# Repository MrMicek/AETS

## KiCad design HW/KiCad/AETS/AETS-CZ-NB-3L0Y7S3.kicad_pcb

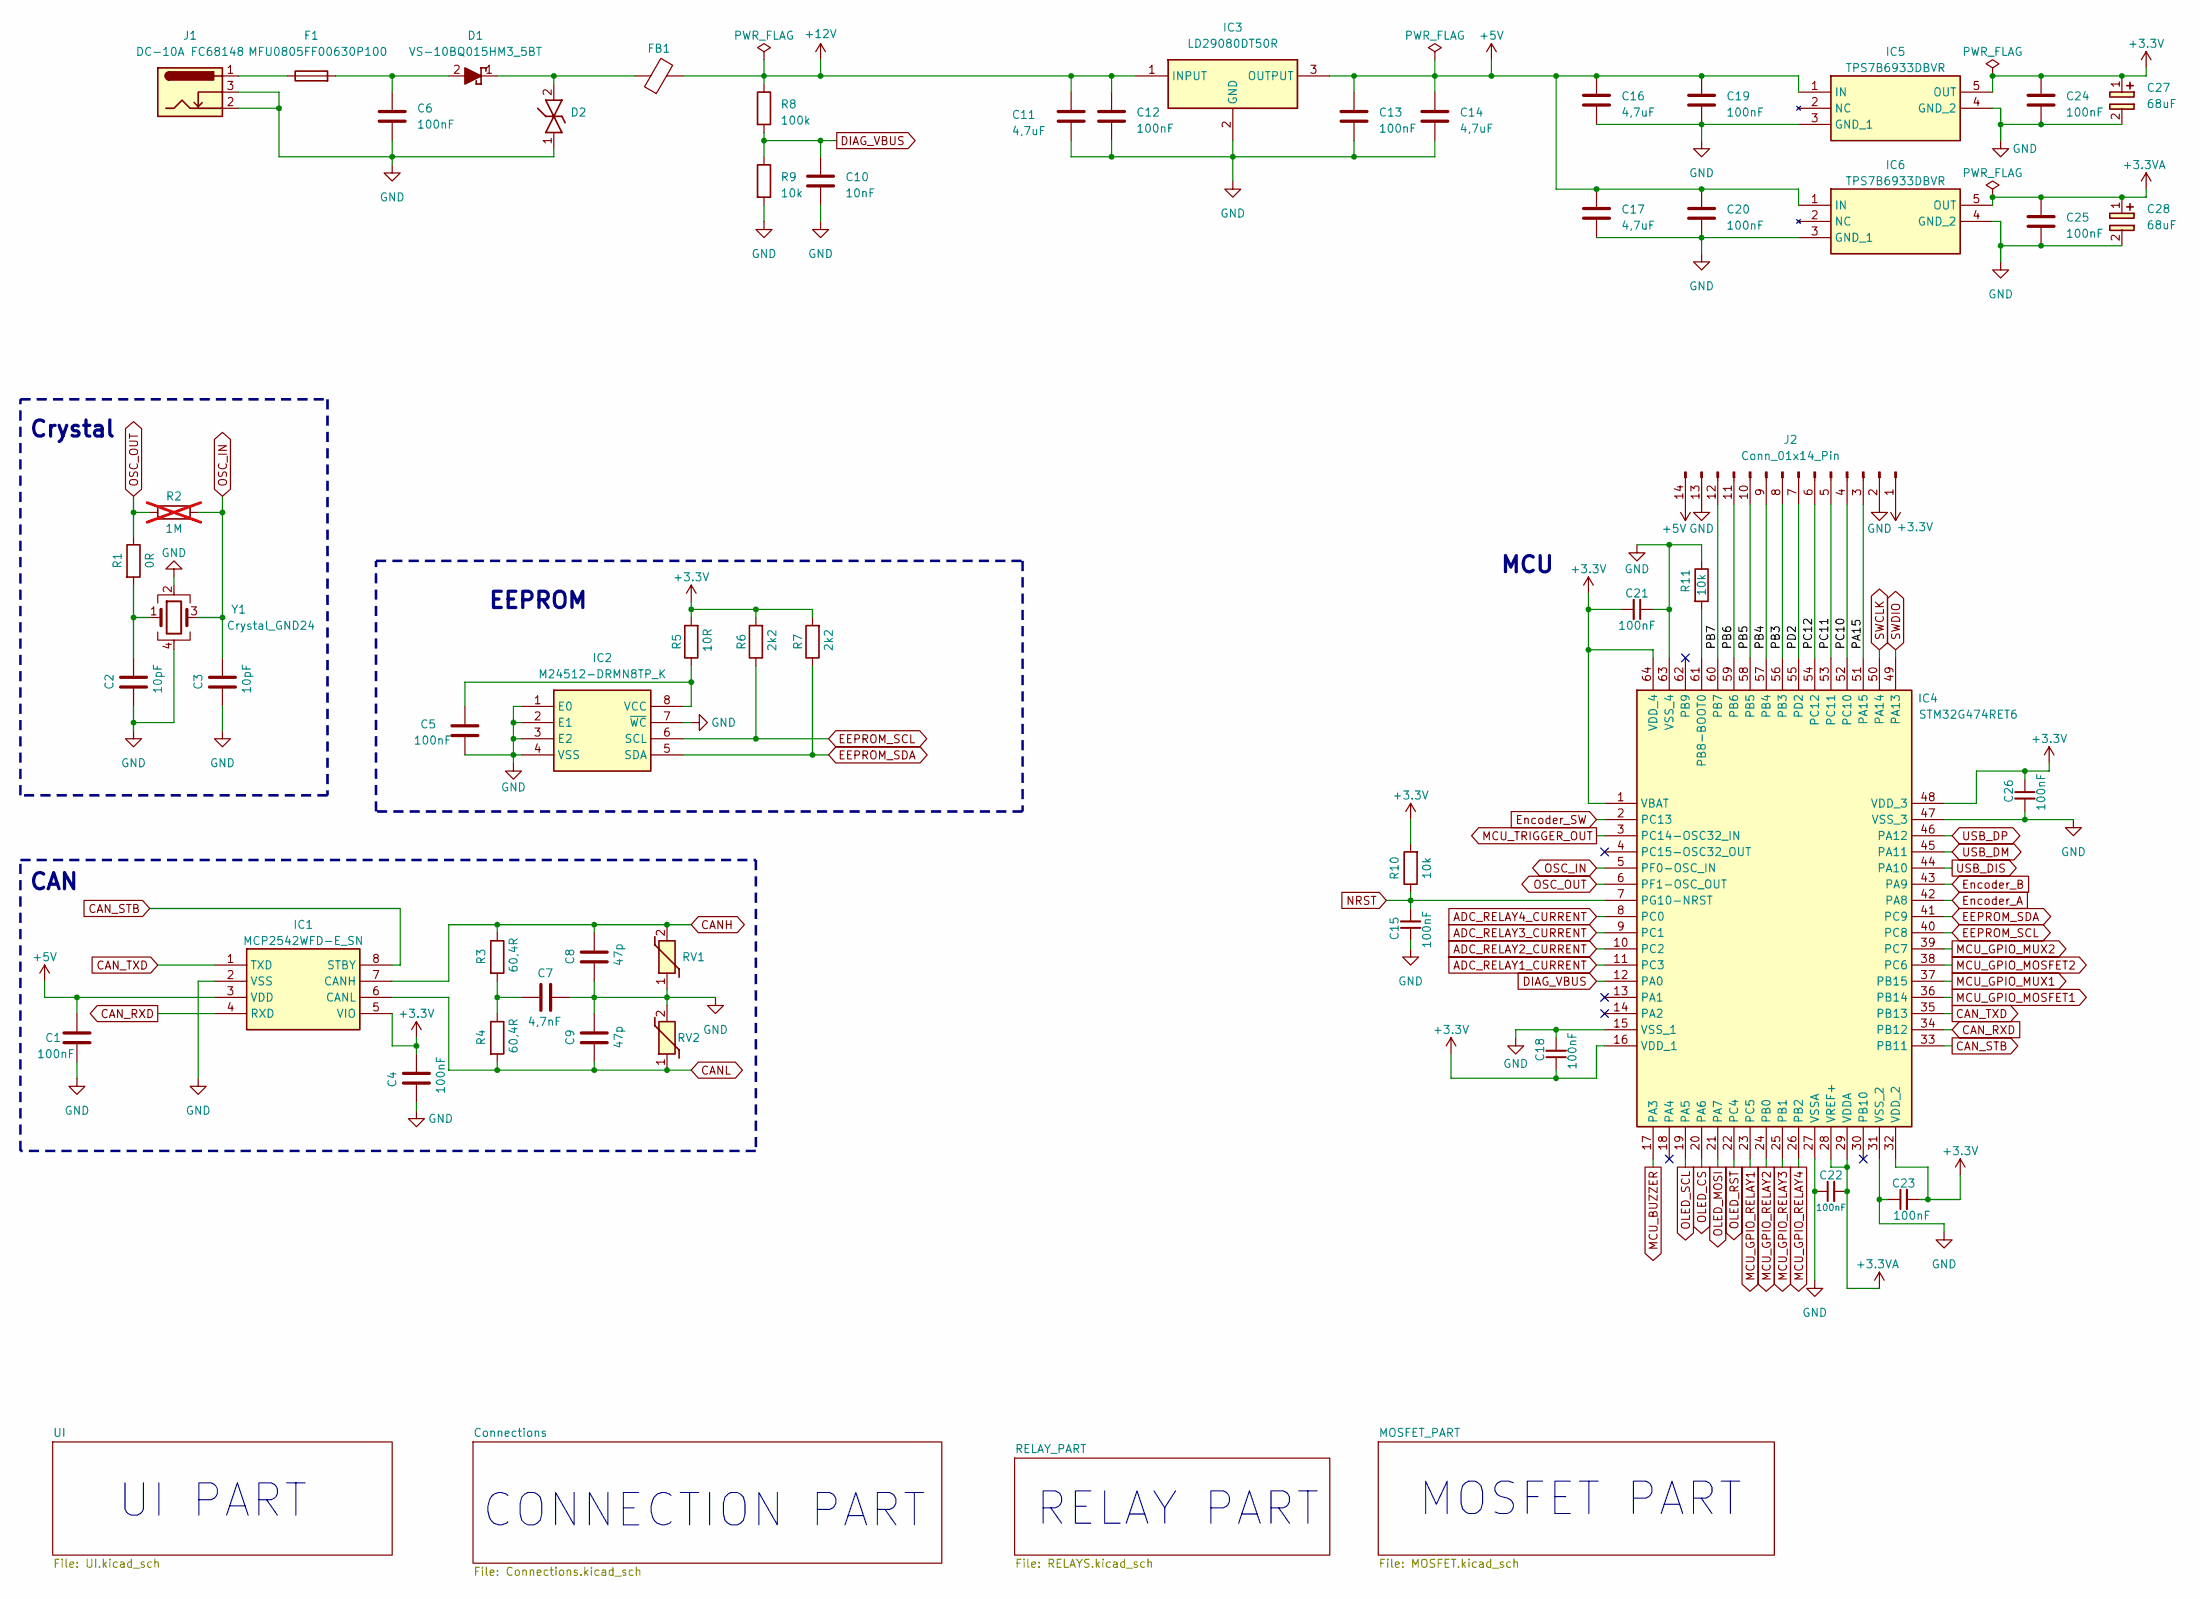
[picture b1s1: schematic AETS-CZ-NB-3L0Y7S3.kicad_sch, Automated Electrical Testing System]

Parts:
C1, C4, C5, C6, C12, C13, C19, C20, C24, C25: 100nF; C_0805_2012Metric
C2, C3: 10pF; C_0603_1608Metric
C7: 4,7nF; C_0805_2012Metric
C8, C9: 47p; C_0805_2012Metric
C10: 10nF; C_0805_2012Metric
C11, C14, C16, C17: 4,7uF; C_1210_3225Metric
C15, C18, C21, C22, C23, C26: 100nF; C_0603_1608Metric
C27, C28: 68uF; EEEHP1H4R7P; Mouser Part Number 667-EEE-FP1C680AL
D1: VS-10BQ015HM3_5BT; DIOM5436X244N; Mouser Part Number 78-VS-10BQ015HM35BT
D2: 1.5B18CA-M3/H; DIOM5436X244N; Manufacturer_Part_Number TESDU5V0 RGG
F1: MFU0805FF00630P100; Fuse_0805_2012Metric
FB1: R_0805_2012Metric_Pad1.20x1.40mm_HandSolder
IC1: MCP2542WFD-E_SN; SOIC127P600X175-8N; Manufacturer_Part_Number MCP2542WFD-E/SN; Mouser Part Number 579-MCP2542WFD-E/SN
IC2: M24512-DRMN8TP_K; SOIC127P600X175-8N; Manufacturer_Part_Number M24512-DRMN8TP/K; Mouser Part Number 511-M24512-DRMN8TP/K
IC3: LD29080DT50R; L4931CDT50TR; Manufacturer_Part_Number L4931CDT50-TR; Mouser Part Number 511-L4931CDT50-TR
IC4: STM32G474RET6; QFP50P1200X1200X160-64N; Manufacturer_Part_Number STM32G474RET6; Mouser Part Number 511-STM32G474RET6
IC5, IC6: TPS7B6933DBVR; SOT95P280X145-5N; Manufacturer_Part_Number TPS7B6950QDBVRQ1; Mouser Part Number 595-TPS7B6950QDBVRQ1
J1: DC-10A FC68148; DC10AFC68148
J2: Conn_01x14_Pin; PinHeader_1x14_P2.54mm_Vertical
R1: 0R; R_0603_1608Metric
R2: 1M; R_0603_1608Metric; not fitted
R3, R4: 60,4R; R_0805_2012Metric
R5: 10R; R_0805_2012Metric
R6, R7: 2k2; R_0805_2012Metric
R8: 100k; R_0805_2012Metric
R9: 10k; R_0805_2012Metric
R10, R11: 10k; R_0603_1608Metric
RV1, RV2: AVR-M1608C270KTACB; VARC1608X90N; Mouser Part Number 810-AVRM1608C270KACB
Y1: Crystal_GND24; ECS4001833JGNTR3

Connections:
+3.3V: C4.1, C18.1, C21.2, C23.2, C24.1, C26.1, C27.1 (+), IC1.5 (VIO), IC4.1 (VBAT), IC4.16 (VDD_1), IC4.32 (VDD_2), IC4.48 (VDD_3), IC4.64 (VDD_4), IC5.5 (OUT), J2.1, R5.2, R6.2, R7.2, R10.2; also elsewhere on the board
+3.3VA: C22.2, C25.1, C28.1 (+), IC4.28 (VREF+), IC4.29 (VDDA), IC6.5 (OUT)
+5V: C1.1, C13.1, C14.1, C16.1, C17.1, C19.1, C20.1, IC1.3 (VDD), IC3.3 (OUTPUT), IC5.1 (IN), IC6.1 (IN), J2.14; also elsewhere on the board
+12V: C11.1, C12.1, FB1.2, IC3.1 (INPUT), R8.1; also elsewhere on the board
/PA15: IC4.51 (PA15), J2.3
/PB3: IC4.56 (PB3), J2.8
/PB4: IC4.57 (PB4), J2.9
/PB5: IC4.58 (PB5), J2.10
/PB6: IC4.59 (PB6), J2.11
/PB7: IC4.60 (PB7), J2.12
/PC10: IC4.52 (PC10), J2.4
/PC11: IC4.53 (PC11), J2.5
/PC12: IC4.54 (PC12), J2.6
/PD2: IC4.55 (PD2), J2.7
ADC_RELAY1_CURRENT: IC4.11 (PC3); also elsewhere on the board
ADC_RELAY2_CURRENT: IC4.10 (PC2); also elsewhere on the board
ADC_RELAY3_CURRENT: IC4.9 (PC1); also elsewhere on the board
ADC_RELAY4_CURRENT: IC4.8 (PC0); also elsewhere on the board
CANH: C8.1, IC1.7 (CANH), R3.1, RV1.2; also elsewhere on the board
CANL: C9.2, IC1.6 (CANL), R4.2, RV2.1; also elsewhere on the board
CAN_RXD: IC1.4 (RXD), IC4.34 (PB12)
CAN_STB: IC1.8 (STBY), IC4.33 (PB11)
CAN_TXD: IC1.1 (TXD), IC4.35 (PB13)
DIAG_VBUS: C10.1, IC4.12 (PA0), R8.2, R9.1
EEPROM_SCL: IC2.6 (SCL), IC4.40 (PC8), R6.1
EEPROM_SDA: IC2.5 (SDA), IC4.41 (PC9), R7.1
Encoder_A: IC4.42 (PA8); also elsewhere on the board
Encoder_B: IC4.43 (PA9); also elsewhere on the board
Encoder_SW: IC4.2 (PC13); also elsewhere on the board
GND: C1.2, C2.2, C3.2, C4.2, C5.2, C6.2, C7.2, C8.2, C9.1, C10.2, C11.2, C12.2, C13.2, C14.2, C15.1, C16.2, C17.2, C18.2, C19.2, C20.2, C21.1, C22.1, C23.1, C24.2, C25.2, C26.2, C27.2 (-), C28.2 (-), D2.1 (K1), IC1.2 (VSS), IC2.1 (E0), IC2.2 (E1), IC2.3 (E2), IC2.4 (VSS), IC2.7 (~WC), IC3.2 (GND), IC4.15 (VSS_1), IC4.27 (VSSA), IC4.31 (VSS_2), IC4.47 (VSS_3), IC4.63 (VSS_4), IC5.3 (GND_1), IC5.4 (GND_2), IC6.3 (GND_1), IC6.4 (GND_2), J1.2, J1.3, J2.2, J2.13, R9.2, R11.1, RV1.1, RV2.2, Y1.2, Y1.4; also elsewhere on the board
MCU_BUZZER: IC4.17 (PA3); also elsewhere on the board
MCU_GPIO_MOSFET1: IC4.36 (PB14); also elsewhere on the board
MCU_GPIO_MOSFET2: IC4.38 (PC6); also elsewhere on the board
MCU_GPIO_MUX1: IC4.37 (PB15); also elsewhere on the board
MCU_GPIO_MUX2: IC4.39 (PC7); also elsewhere on the board
MCU_GPIO_RELAY1: IC4.23 (PC5); also elsewhere on the board
MCU_GPIO_RELAY2: IC4.24 (PB0); also elsewhere on the board
MCU_GPIO_RELAY3: IC4.25 (PB1); also elsewhere on the board
MCU_GPIO_RELAY4: IC4.26 (PB2); also elsewhere on the board
MCU_TRIGGER_OUT: IC4.3 (PC14-OSC32_IN); also elsewhere on the board
NRST: C15.2, IC4.7 (PG10-NRST), R10.1; also elsewhere on the board
unnamed: C2.1, R1.2, Y1.1
unnamed: C7.1, R3.2, R4.1
unnamed: C6.1, D1.2 (A), F1.2
unnamed: D1.1 (K), D2.2 (K2), FB1.1
unnamed: F1.1, J1.1
unnamed: C5.1, IC2.8 (VCC), R5.1
unnamed: IC4.61 (PB8-BOOT0), R11.2
OLED_CS: IC4.20 (PA6); also elsewhere on the board
OLED_MOSI: IC4.21 (PA7); also elsewhere on the board
OLED_RST: IC4.22 (PC4); also elsewhere on the board
OLED_SCL: IC4.19 (PA5); also elsewhere on the board
OSC_IN: C3.1, IC4.5 (PF0-OSC_IN), R2.2, Y1.3
OSC_OUT: IC4.6 (PF1-OSC_OUT), R1.1, R2.1
SWCLK: IC4.50 (PA14); also elsewhere on the board
SWDIO: IC4.49 (PA13); also elsewhere on the board
USB_DIS: IC4.44 (PA10); also elsewhere on the board
USB_DM: IC4.45 (PA11); also elsewhere on the board
USB_DP: IC4.46 (PA12); also elsewhere on the board

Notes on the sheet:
MOSFET PART
RELAY PART
MCU
Crystal
UI PART
CAN
EEPROM
CONNECTION PART

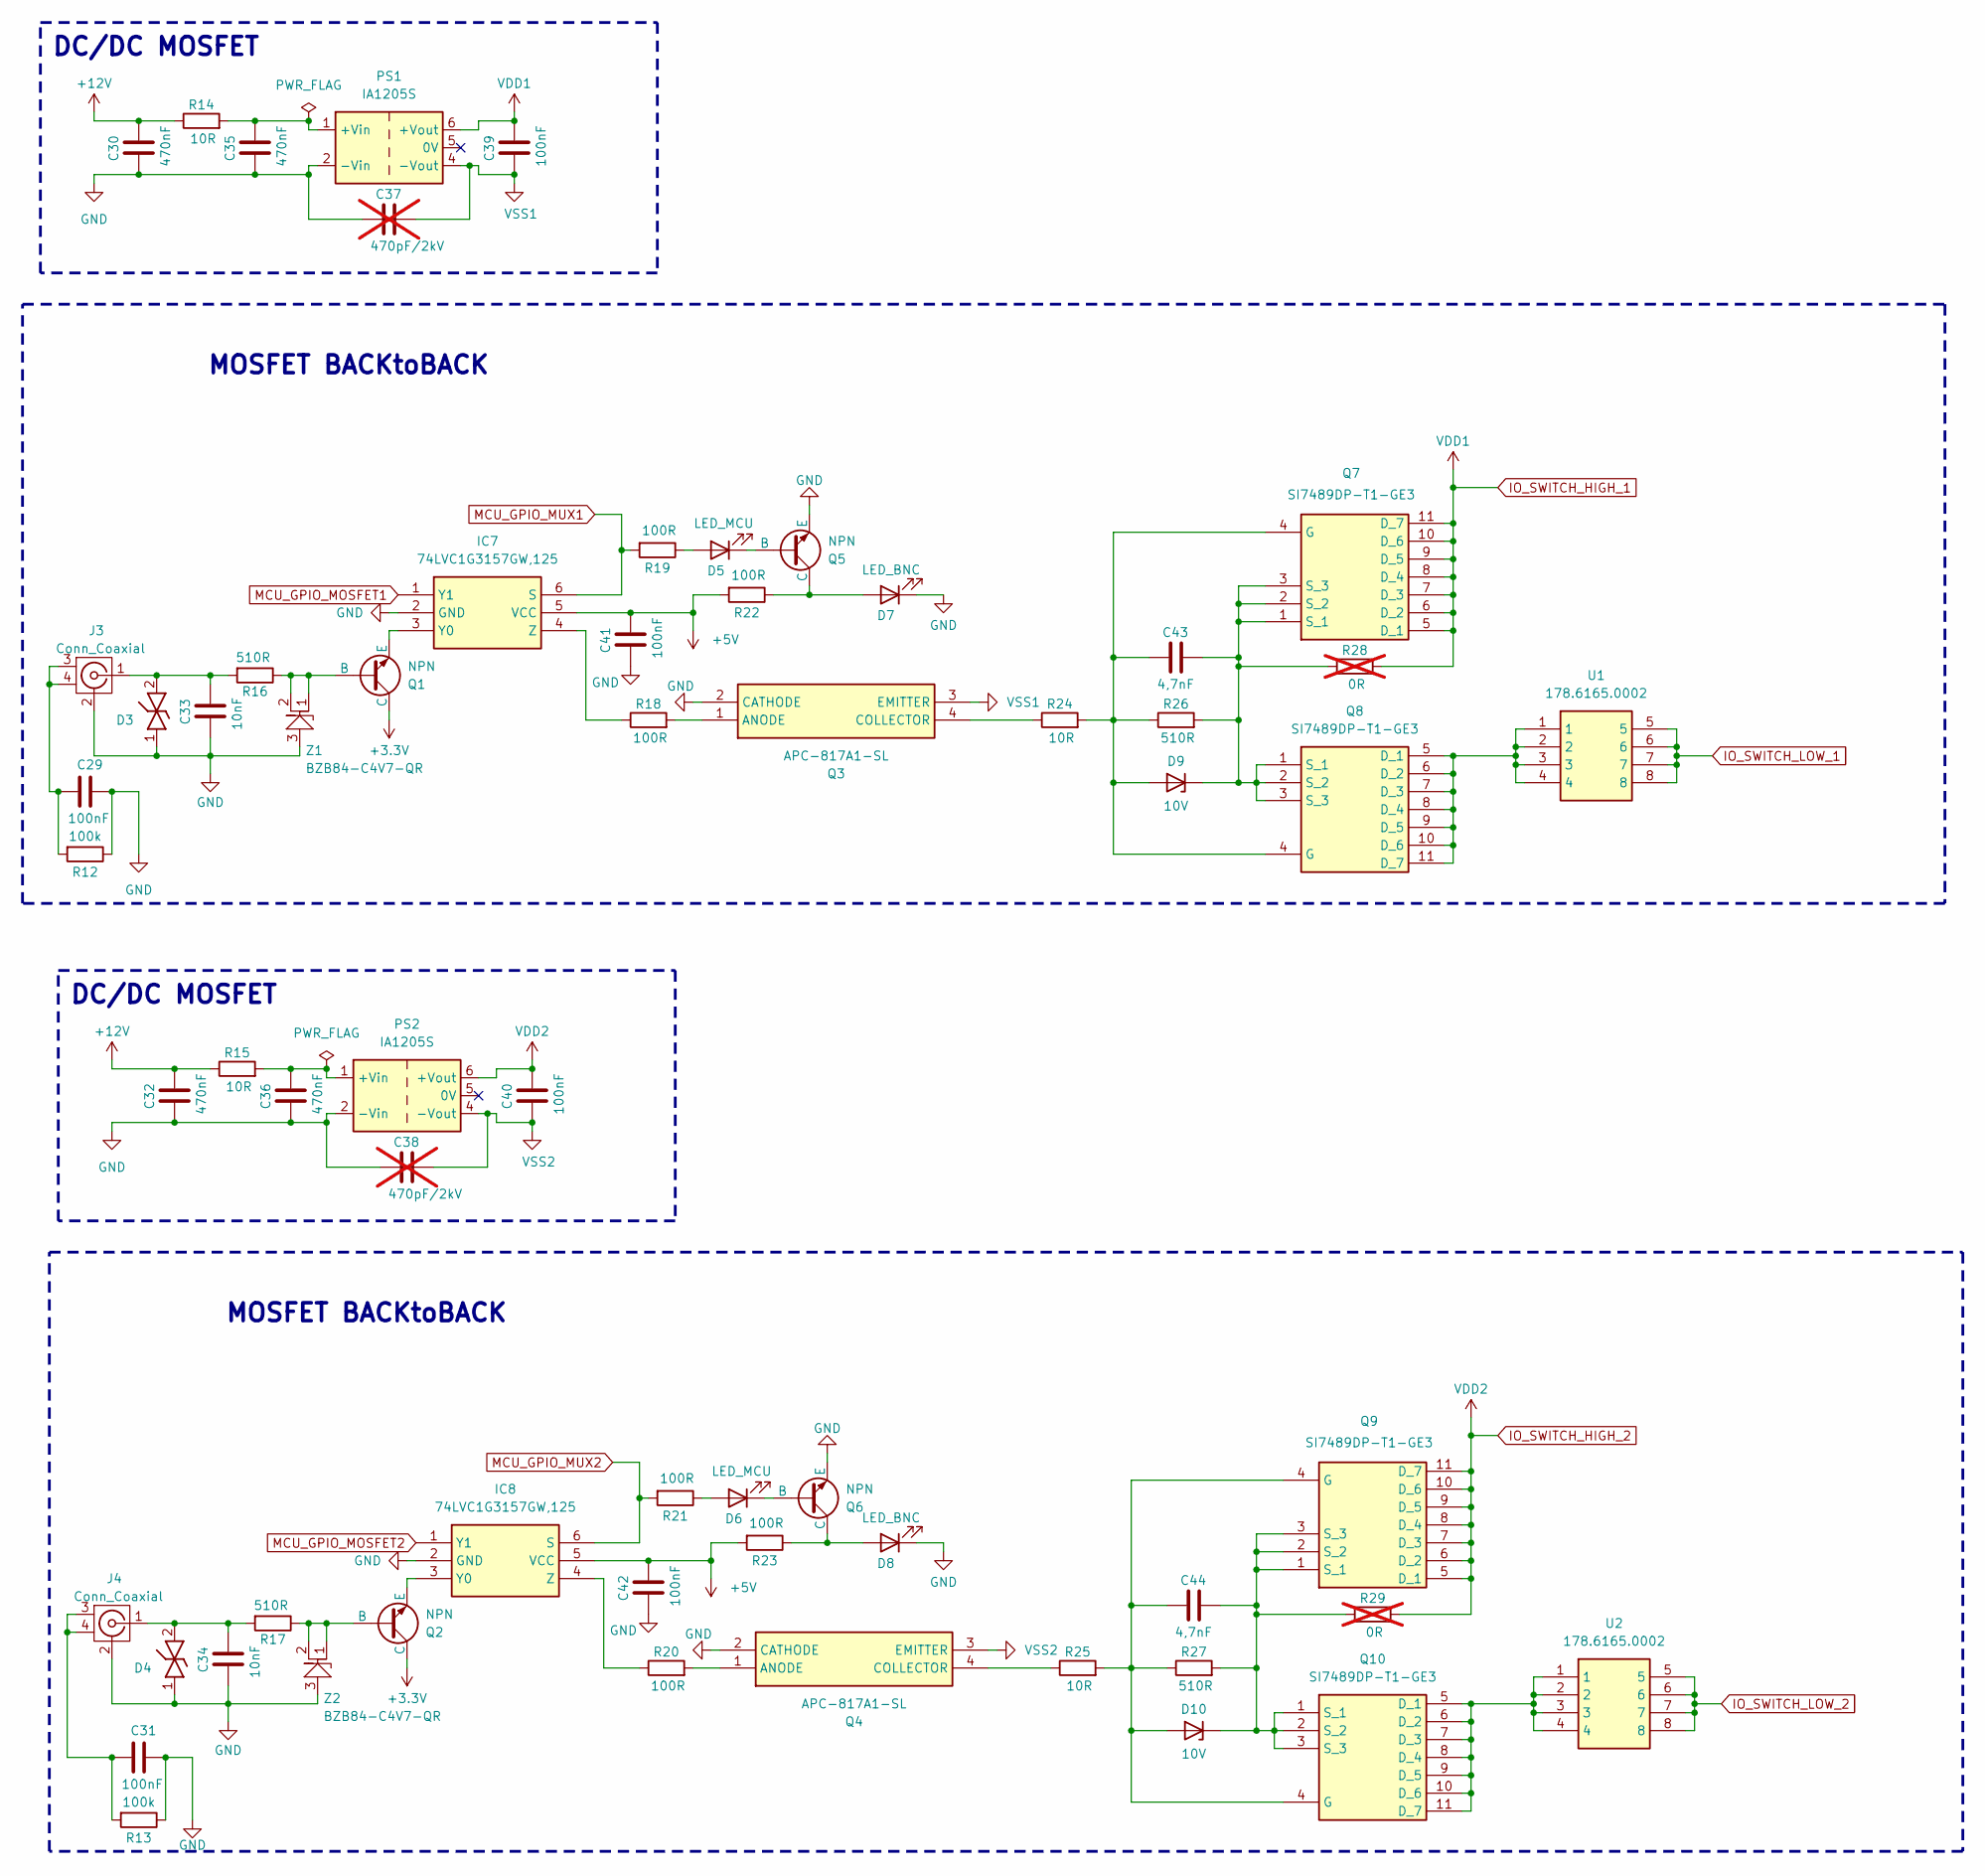
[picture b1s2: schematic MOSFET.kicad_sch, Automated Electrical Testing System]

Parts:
C29, C31, C39, C40, C41, C42: 100nF; C_0805_2012Metric
C30, C32, C35, C36: 470nF; C_0805_2012Metric
C33, C34: 10nF; C_0805_2012Metric
C37, C38: 470pF/2kV; C_1210_3225Metric; not fitted
C43, C44: 4,7nF; C_0805_2012Metric
D3, D4: TESDU5V0 RGG; DIONC1608X70N; Manufacturer_Part_Number TESDU5V0 RGG
D5, D6: LED_MCU; LED_D3.0mm
D7, D8: LED_BNC; LED_D3.0mm
D9, D10: 10V; SODFL5026X125N
IC7, IC8: 74LVC1G3157GW,125; 74LVC1G3157GW125; Manufacturer_Part_Number 74LVC1G3157GW,125; Mouser Part Number 771-LVC1G3157GW125
J3, J4: Conn_Coaxial; VBI211
PS1, PS2: IA1205S; Converter_DCDC_XP_POWER-IAxxxxS_THT
Q1, Q2, Q5, Q6: NPN; SOT95P240X120-3N
Q3, Q4: APC-817A1-SL; APC817A1SL; Manufacturer_Part_Number APC-817A1-SL
Q7, Q8, Q9, Q10: SI7489DP-T1-GE3; SI7141DPT1GE3; Manufacturer_Part_Number SI7489DP-T1-GE3; Mouser Part Number 781-SI7489DP-T1-GE3
R12, R13: 100k; R_0805_2012Metric
R14, R15, R24, R25: 10R; R_0805_2012Metric
R16, R17, R26, R27: 510R; R_0805_2012Metric
R18, R19, R20, R21, R22, R23: 100R; R_0805_2012Metric
R28, R29: 0R; R_0603_1608Metric; not fitted
U1, U2: 178.6165.0002; 17861650002; Mouser Part Number 576-178.6165.0002
Z1, Z2: BZB84-C4V7-QR; SOT95P230X110-3N; Manufacturer_Part_Number BZB84-C4V7-QR

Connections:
+3.3V: Q1.3 (C), Q2.3 (C); also elsewhere on the board
+5V: C41.1, C42.1, IC7.5 (VCC), IC8.5 (VCC), R22.2, R23.2; also elsewhere on the board
+12V: C30.1, C32.1, R14.1, R15.1; also elsewhere on the board
GND: C29.1, C30.2, C31.1, C32.2, C33.2, C34.2, C35.2, C36.2, C37.2, C38.2, C41.2, C42.2, D3.1 (K1), D4.1 (K1), D7.1 (K), D8.1 (K), IC7.2 (GND), IC8.2 (GND), J3.2 (Ext), J4.2 (Ext), PS1.2 (-Vin), PS2.2 (-Vin), Q3.2 (CATHODE), Q4.2 (CATHODE), Q5.2 (E), Q6.2 (E), R12.1, R13.1, Z1.3, Z2.3; also elsewhere on the board
IO_SWITCH_HIGH_1: C39.1, PS1.6 (+Vout), Q7.5 (D_1), Q7.6 (D_2), Q7.7 (D_3), Q7.8 (D_4), Q7.9 (D_5), Q7.10 (D_6), Q7.11 (D_7), R28.2; also elsewhere on the board
IO_SWITCH_HIGH_2: C40.1, PS2.6 (+Vout), Q9.5 (D_1), Q9.6 (D_2), Q9.7 (D_3), Q9.8 (D_4), Q9.9 (D_5), Q9.10 (D_6), Q9.11 (D_7), R29.2; also elsewhere on the board
IO_SWITCH_LOW_1: U1.5, U1.6, U1.7, U1.8; also elsewhere on the board
IO_SWITCH_LOW_2: U2.5, U2.6, U2.7, U2.8; also elsewhere on the board
MCU_GPIO_MOSFET1: IC7.1 (Y1); also elsewhere on the board
MCU_GPIO_MOSFET2: IC8.1 (Y1); also elsewhere on the board
MCU_GPIO_MUX1: IC7.6 (S), R19.2; also elsewhere on the board
MCU_GPIO_MUX2: IC8.6 (S), R21.2; also elsewhere on the board
unnamed: C29.2, J3.3, J3.4, R12.2
unnamed: C31.2, J4.3, J4.4, R13.2
unnamed: C33.1, D3.2 (K2), J3.1 (In), R16.2
unnamed: C34.1, D4.2 (K2), J4.1 (In), R17.2
unnamed: D5.2 (A), R19.1
unnamed: D5.1 (K), Q5.1 (B)
unnamed: D6.2 (A), R21.1
unnamed: D6.1 (K), Q6.1 (B)
unnamed: D7.2 (A), Q5.3 (C), R22.1
unnamed: D8.2 (A), Q6.3 (C), R23.1
unnamed: C43.2, D9.2 (A), Q7.4 (G), Q8.4 (G), R24.2, R26.1
unnamed: C43.1, D9.1 (K), Q7.1 (S_1), Q7.2 (S_2), Q7.3 (S_3), Q8.1 (S_1), Q8.2 (S_2), Q8.3 (S_3), R26.2, R28.1
unnamed: C44.2, D10.2 (A), Q9.4 (G), Q10.4 (G), R25.2, R27.1
unnamed: C44.1, D10.1 (K), Q9.1 (S_1), Q9.2 (S_2), Q9.3 (S_3), Q10.1 (S_1), Q10.2 (S_2), Q10.3 (S_3), R27.2, R29.1
unnamed: IC7.3 (Y0), Q1.2 (E)
unnamed: IC7.4 (Z), R18.1
unnamed: IC8.3 (Y0), Q2.2 (E)
unnamed: IC8.4 (Z), R20.1
unnamed: C35.1, PS1.1 (+Vin), R14.2
unnamed: C36.1, PS2.1 (+Vin), R15.2
unnamed: Q1.1 (B), R16.1, Z1.1, Z1.2
unnamed: Q2.1 (B), R17.1, Z2.1, Z2.2
unnamed: Q3.1 (ANODE), R18.2
unnamed: Q3.4 (COLLECTOR), R24.1
unnamed: Q4.1 (ANODE), R20.2
unnamed: Q4.4 (COLLECTOR), R25.1
unnamed: Q8.5 (D_1), Q8.6 (D_2), Q8.7 (D_3), Q8.8 (D_4), Q8.9 (D_5), Q8.10 (D_6), Q8.11 (D_7), U1.1, U1.2, U1.3, U1.4
unnamed: Q10.5 (D_1), Q10.6 (D_2), Q10.7 (D_3), Q10.8 (D_4), Q10.9 (D_5), Q10.10 (D_6), Q10.11 (D_7), U2.1, U2.2, U2.3, U2.4
VSS1: C37.1, C39.2, PS1.4 (-Vout), Q3.3 (EMITTER)
VSS2: C38.1, C40.2, PS2.4 (-Vout), Q4.3 (EMITTER)

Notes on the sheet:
MOSFET BACKtoBACK
DC/DC MOSFET

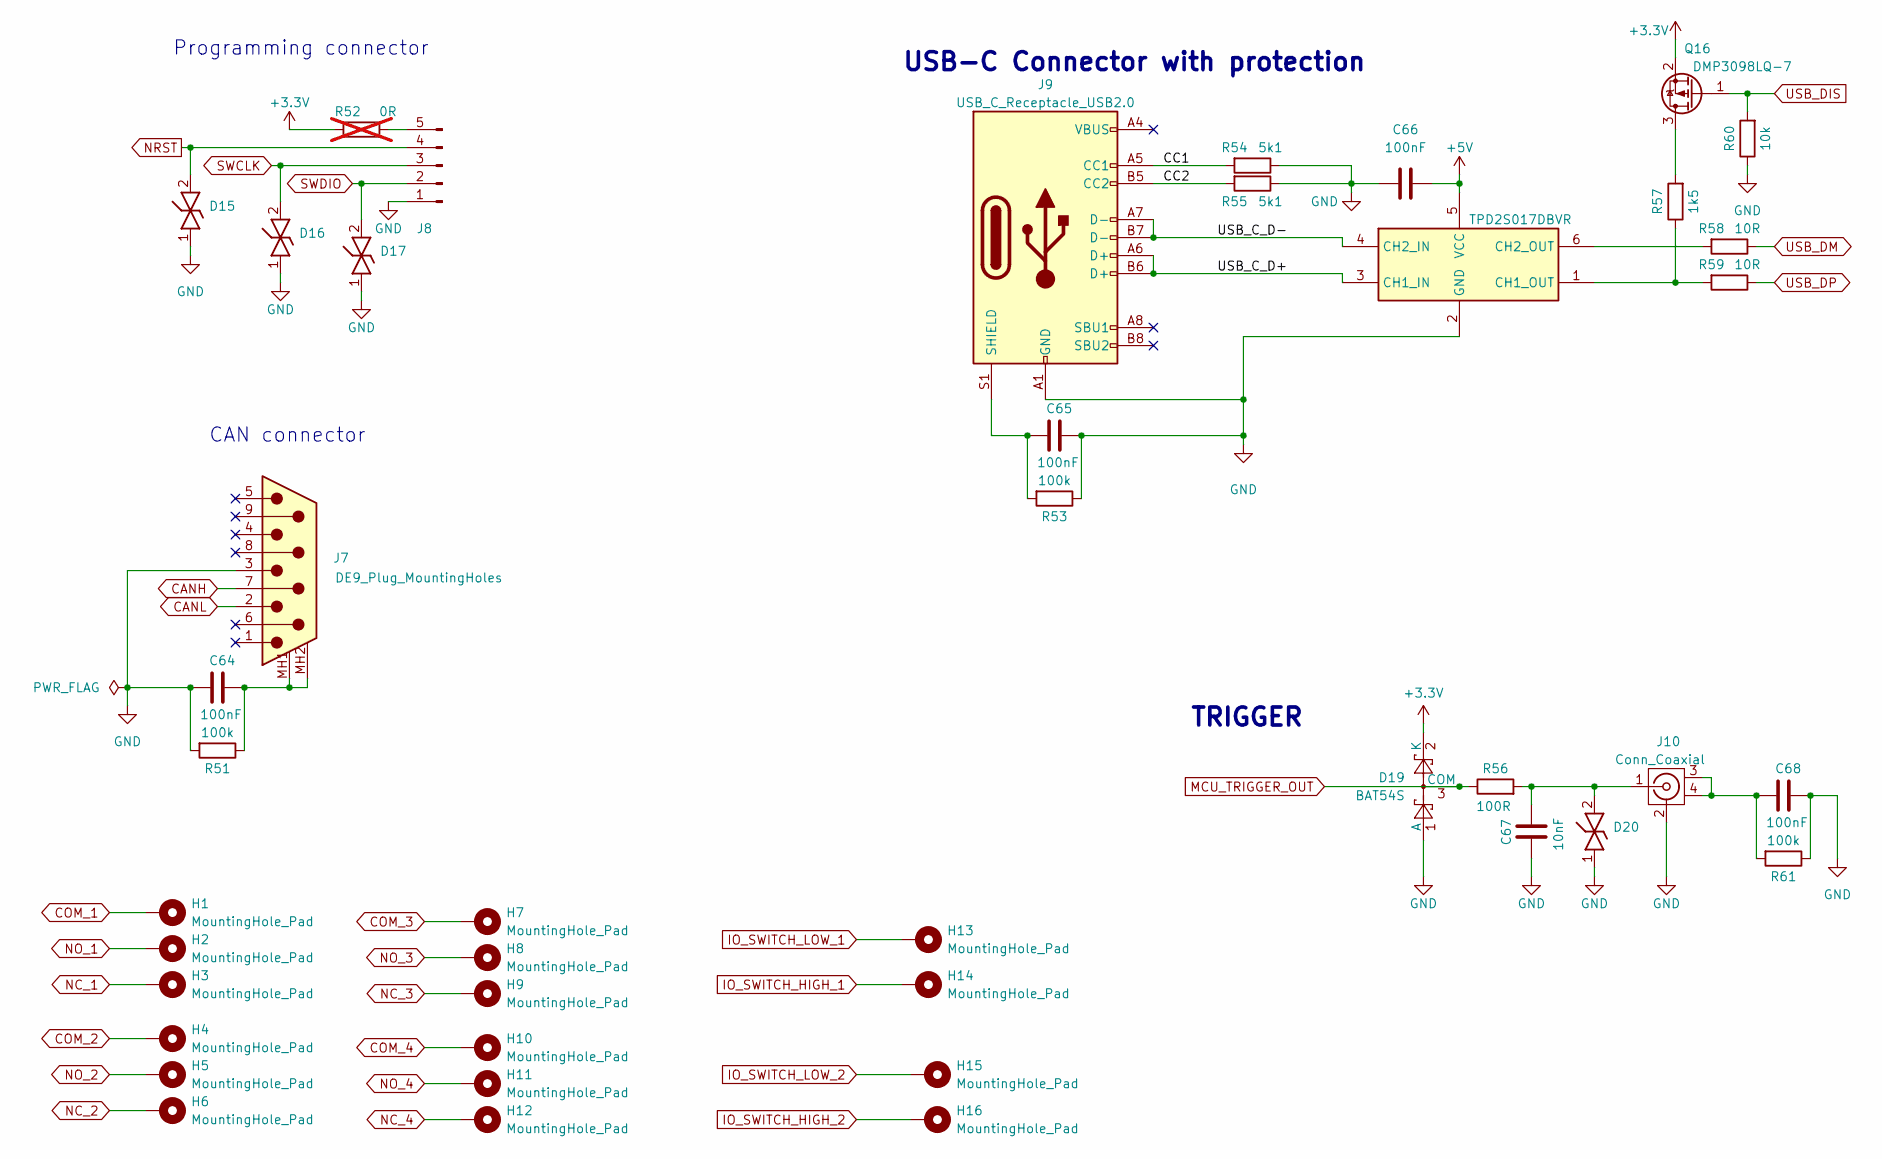
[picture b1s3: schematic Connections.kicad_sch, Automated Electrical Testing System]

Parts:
C64, C65, C66, C68: 100nF; C_0805_2012Metric
C67: 10nF; C_0805_2012Metric
D15, D16, D17, D20: TESDU5V0 RGG; DIONC1608X70N; Manufacturer_Part_Number TESDU5V0 RGG
D18: TPD2S017DBVR; SOT95P280X145-6N; Manufacturer_Part_Number TPD2S017DBVR; Mouser Part Number 595-TPD2S017DBVR
D19: BAT54S; SOT-23
H1, H2, H3, H4, H5, H6, H7, H8, H9, H10, H11, H12, H13, H14, H15, H16: MountingHole_Pad; MountingHole_2.2mm_M2_Pad_Via
J7: DE9_Plug_MountingHoles; G17C0910132EU
J8: Conn_01x05_Pin; PinHeader_1x05_P2.54mm_Vertical
J9: USB_C_Receptacle_USB2.0; USB_C_Receptacle_GCT_USB4105-xx-A_16P_TopMnt_Horizontal
J10: Conn_Coaxial; VBI211
Q16: DMP3098LQ-7; SOT96P240X110-3N
R51, R53, R61: 100k; R_0805_2012Metric
R52: 0R; R_0603_1608Metric; not fitted
R54, R55: 5k1; R_0805_2012Metric
R56: 100R; R_0805_2012Metric
R57: 1k5; R_0603_1608Metric
R58, R59: 10R; R_0805_2012Metric
R60: 10k; R_0805_2012Metric

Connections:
+3.3V: D19.2 (K), Q16.2 (S), R52.1; also elsewhere on the board
+5V: C66.2, D18.5 (VCC); also elsewhere on the board
/Connections/CC1: J9.A5 (CC1), R54.2
/Connections/CC2: J9.B5 (CC2), R55.2
/Connections/USB_C_D+: D18.3 (CH1_IN), J9.A6 (D+), J9.B6 (D+)
/Connections/USB_C_D-: D18.4 (CH2_IN), J9.A7 (D-), J9.B7 (D-)
CANH: J7.7; also elsewhere on the board
CANL: J7.2; also elsewhere on the board
COM_1: H1.1; also elsewhere on the board
COM_2: H4.1; also elsewhere on the board
COM_3: H7.1; also elsewhere on the board
COM_4: H10.1; also elsewhere on the board
GND: C64.2, C65.1, C66.1, C67.2, C68.1, D15.1 (K1), D16.1 (K1), D17.1 (K1), D18.2 (GND), D19.1 (A), D20.1 (K1), J7.3, J8.1, J9.A1 (GND), J9.A12 (GND), J9.B1 (GND), J9.B12 (GND), J10.2 (Ext), R51.2, R53.1, R54.1, R55.1, R60.1, R61.1; also elsewhere on the board
IO_SWITCH_HIGH_1: H14.1; also elsewhere on the board
IO_SWITCH_HIGH_2: H16.1; also elsewhere on the board
IO_SWITCH_LOW_1: H13.1; also elsewhere on the board
IO_SWITCH_LOW_2: H15.1; also elsewhere on the board
MCU_TRIGGER_OUT: D19.3 (COM), R56.1; also elsewhere on the board
NC_1: H3.1; also elsewhere on the board
NC_2: H6.1; also elsewhere on the board
NC_3: H9.1; also elsewhere on the board
NC_4: H12.1; also elsewhere on the board
NO_1: H2.1; also elsewhere on the board
NO_2: H5.1; also elsewhere on the board
NO_3: H8.1; also elsewhere on the board
NO_4: H11.1; also elsewhere on the board
NRST: D15.2 (K2), J8.4; also elsewhere on the board
unnamed: C64.1, J7.MH1 (PAD), J7.MH2 (PAD), R51.1
unnamed: C68.2, J10.3, J10.4, R61.2
unnamed: D18.1 (CH1_OUT), R57.1, R59.2
unnamed: D18.6 (CH2_OUT), R58.2
unnamed: C67.1, D20.2 (K2), J10.1 (In), R56.2
unnamed: J8.5, R52.2
unnamed: C65.2, J9.S1 (SHIELD), R53.2
unnamed: Q16.3 (D), R57.2
SWCLK: D16.2 (K2), J8.3; also elsewhere on the board
SWDIO: D17.2 (K2), J8.2; also elsewhere on the board
USB_DIS: Q16.1 (G), R60.2; also elsewhere on the board
USB_DM: R58.1; also elsewhere on the board
USB_DP: R59.1; also elsewhere on the board

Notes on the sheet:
Programming connector
TRIGGER
USB-C Connector with protection
CAN connector

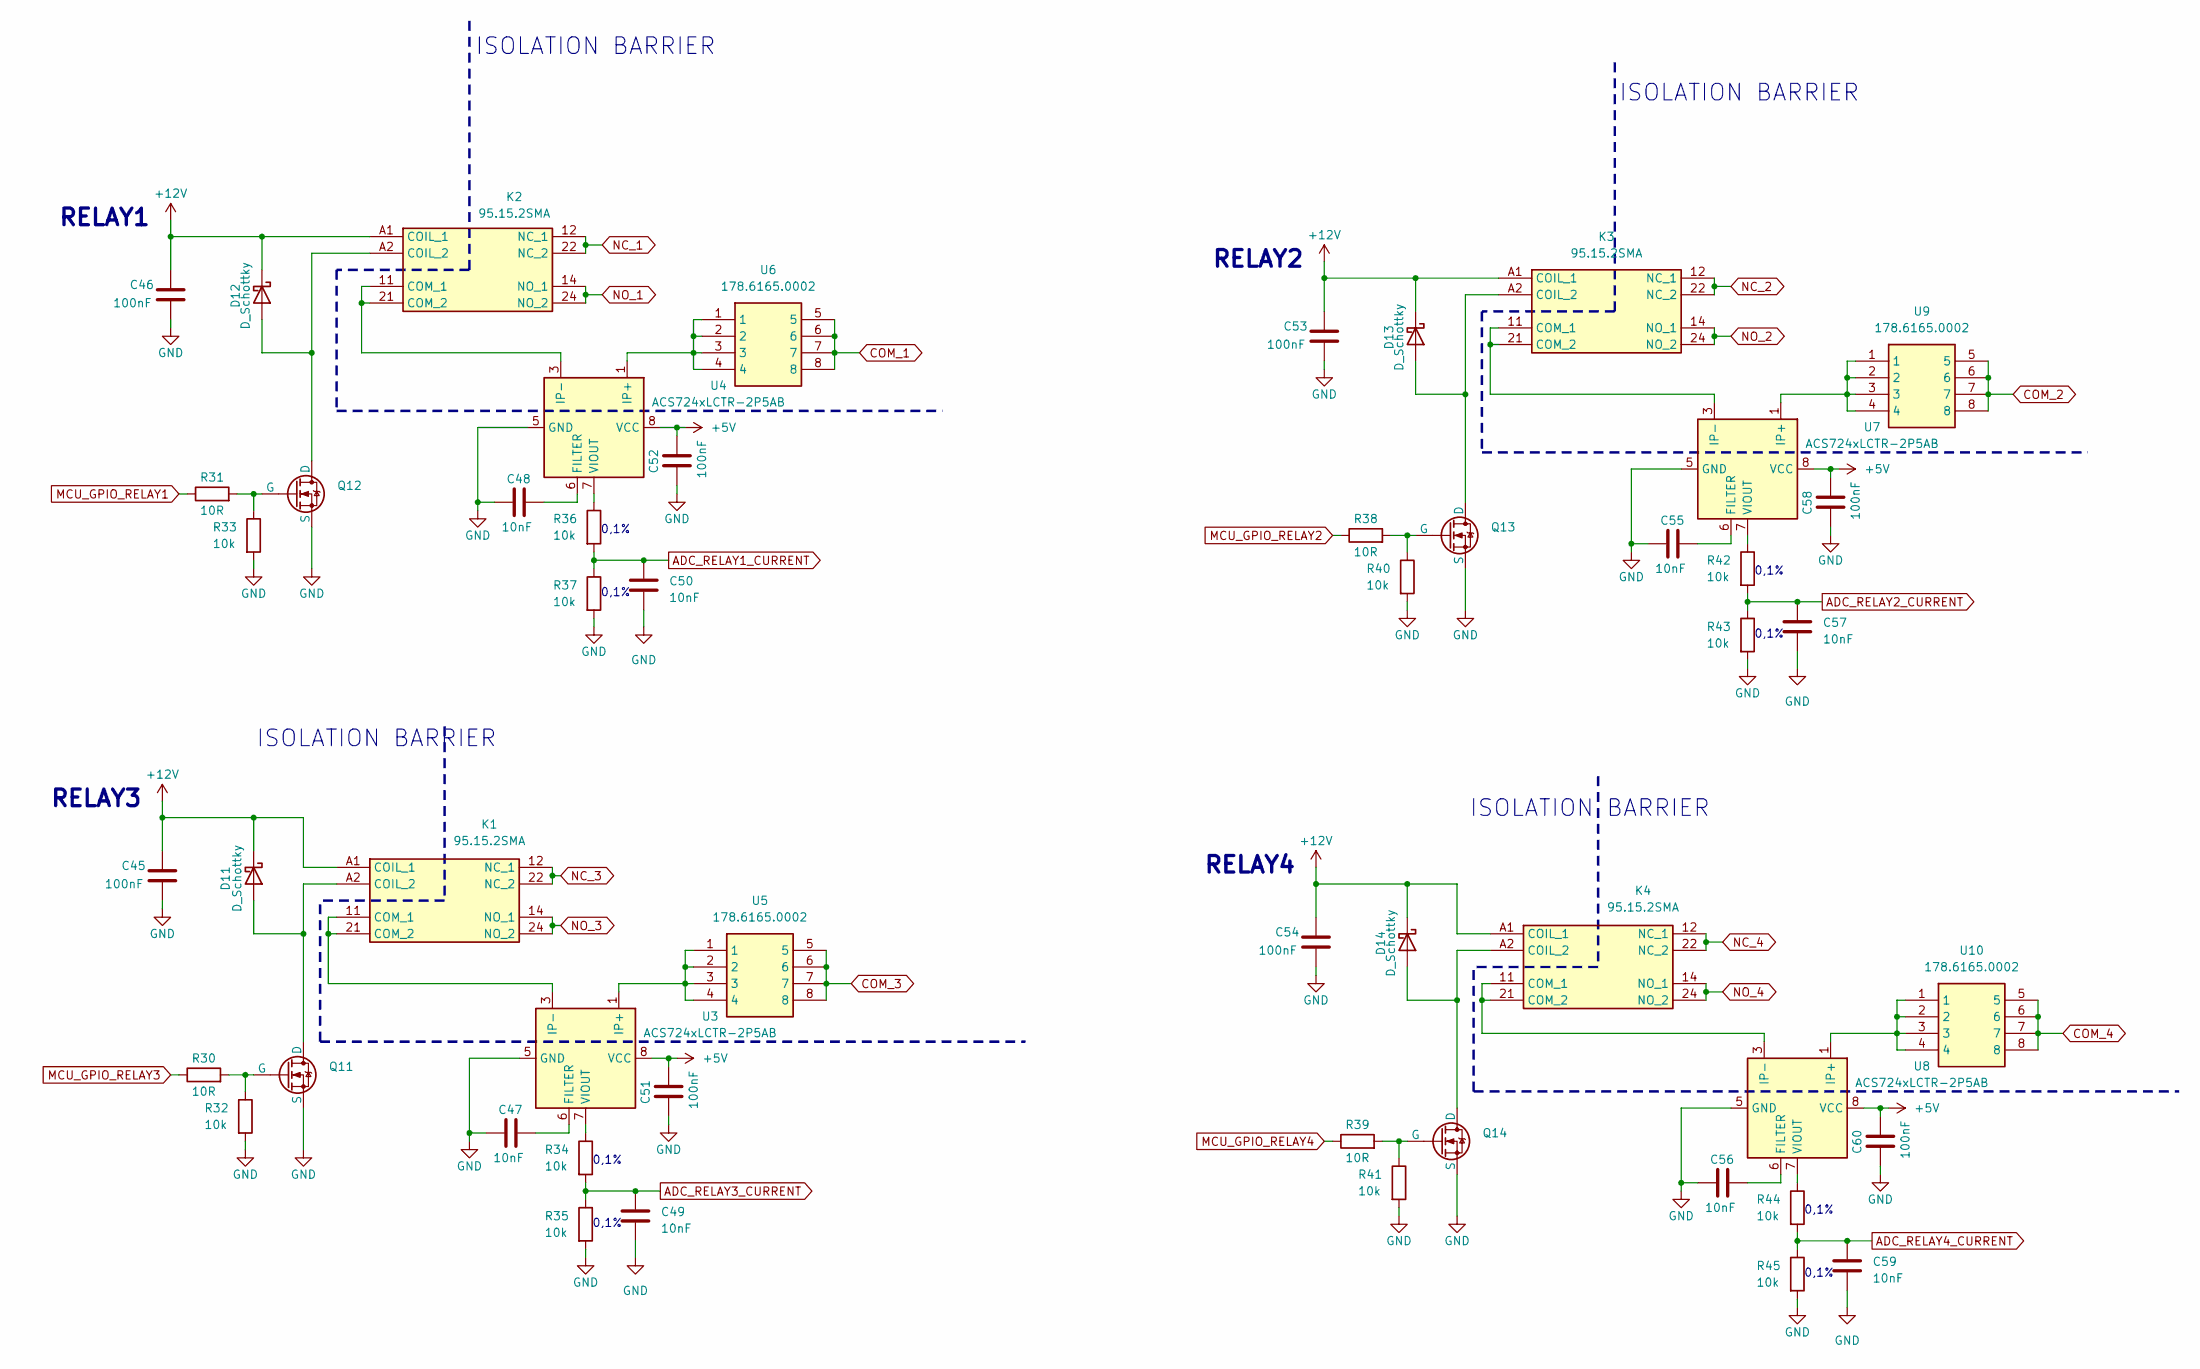
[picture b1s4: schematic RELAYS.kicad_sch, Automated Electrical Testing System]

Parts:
C45, C46, C51, C52, C53, C54, C58, C60: 100nF; C_0805_2012Metric
C47, C48, C49, C50, C55, C56, C57, C59: 10nF; C_0805_2012Metric
D11, D12, D13, D14: D_Schottky; SODFL3616X98N
K1, K2, K3, K4: 95.15.2SMA; 95152SMA; Manufacturer_Part_Number 95.15.2SMA
Q11, Q12, Q13, Q14: NMOS; SOT96P240X110-3N
R30, R31, R38, R39: 10R; R_0805_2012Metric
R32, R33, R34, R35, R36, R37, R40, R41, R42, R43, R44, R45: 10k; R_0805_2012Metric
U3, U4, U7, U8: ACS724xLCTR-2P5AB; SOIC-8_3.9x4.9mm_P1.27mm
U5, U6, U9, U10: 178.6165.0002; 17861650002; Mouser Part Number 576-178.6165.0002

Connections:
+5V: C51.1, C52.1, C58.1, C60.1, U3.8 (VCC), U4.8 (VCC), U7.8 (VCC), U8.8 (VCC); also elsewhere on the board
+12V: C45.1, C46.1, C53.1, C54.1, D11.1 (K), D12.1 (K), D13.1 (K), D14.1 (K), K1.A1 (COIL_1), K2.A1 (COIL_1), K3.A1 (COIL_1), K4.A1 (COIL_1); also elsewhere on the board
ADC_RELAY1_CURRENT: C50.1, R36.2, R37.1; also elsewhere on the board
ADC_RELAY2_CURRENT: C57.1, R42.2, R43.1; also elsewhere on the board
ADC_RELAY3_CURRENT: C49.1, R34.2, R35.1; also elsewhere on the board
ADC_RELAY4_CURRENT: C59.1, R44.2, R45.1; also elsewhere on the board
COM_1: U6.5, U6.6, U6.7, U6.8; also elsewhere on the board
COM_2: U9.5, U9.6, U9.7, U9.8; also elsewhere on the board
COM_3: U5.5, U5.6, U5.7, U5.8; also elsewhere on the board
COM_4: U10.5, U10.6, U10.7, U10.8; also elsewhere on the board
GND: C45.2, C46.2, C47.2, C48.2, C49.2, C50.2, C51.2, C52.2, C53.2, C54.2, C55.2, C56.2, C57.2, C58.2, C59.2, C60.2, Q11.2 (S), Q12.2 (S), Q13.2 (S), Q14.2 (S), R32.2, R33.2, R35.2, R37.2, R40.2, R41.2, R43.2, R45.2, U3.5 (GND), U4.5 (GND), U7.5 (GND), U8.5 (GND); also elsewhere on the board
MCU_GPIO_RELAY1: R31.1; also elsewhere on the board
MCU_GPIO_RELAY2: R38.1; also elsewhere on the board
MCU_GPIO_RELAY3: R30.1; also elsewhere on the board
MCU_GPIO_RELAY4: R39.1; also elsewhere on the board
NC_1: K2.12 (NC_1), K2.22 (NC_2); also elsewhere on the board
NC_2: K3.12 (NC_1), K3.22 (NC_2); also elsewhere on the board
NC_3: K1.12 (NC_1), K1.22 (NC_2); also elsewhere on the board
NC_4: K4.12 (NC_1), K4.22 (NC_2); also elsewhere on the board
NO_1: K2.14 (NO_1), K2.24 (NO_2); also elsewhere on the board
NO_2: K3.14 (NO_1), K3.24 (NO_2); also elsewhere on the board
NO_3: K1.14 (NO_1), K1.24 (NO_2); also elsewhere on the board
NO_4: K4.14 (NO_1), K4.24 (NO_2); also elsewhere on the board
unnamed: D11.2 (A), K1.A2 (COIL_2), Q11.3 (D)
unnamed: D12.2 (A), K2.A2 (COIL_2), Q12.3 (D)
unnamed: D13.2 (A), K3.A2 (COIL_2), Q13.3 (D)
unnamed: D14.2 (A), K4.A2 (COIL_2), Q14.3 (D)
unnamed: K1.11 (COM_1), K1.21 (COM_2), U3.3 (IP-), U3.4 (IP-)
unnamed: K2.11 (COM_1), K2.21 (COM_2), U4.3 (IP-), U4.4 (IP-)
unnamed: K3.11 (COM_1), K3.21 (COM_2), U7.3 (IP-), U7.4 (IP-)
unnamed: K4.11 (COM_1), K4.21 (COM_2), U8.3 (IP-), U8.4 (IP-)
unnamed: Q11.1 (G), R30.2, R32.1
unnamed: Q12.1 (G), R31.2, R33.1
unnamed: Q13.1 (G), R38.2, R40.1
unnamed: Q14.1 (G), R39.2, R41.1
unnamed: C47.1, U3.6 (FILTER)
unnamed: U3.1 (IP+), U3.2 (IP+), U5.1, U5.2, U5.3, U5.4
unnamed: R34.1, U3.7 (VIOUT)
unnamed: C48.1, U4.6 (FILTER)
unnamed: U4.1 (IP+), U4.2 (IP+), U6.1, U6.2, U6.3, U6.4
unnamed: R36.1, U4.7 (VIOUT)
unnamed: C55.1, U7.6 (FILTER)
unnamed: U7.1 (IP+), U7.2 (IP+), U9.1, U9.2, U9.3, U9.4
unnamed: R42.1, U7.7 (VIOUT)
unnamed: C56.1, U8.6 (FILTER)
unnamed: R44.1, U8.7 (VIOUT)
unnamed: U8.1 (IP+), U8.2 (IP+), U10.1, U10.2, U10.3, U10.4

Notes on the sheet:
0,1%
RELAY3
RELAY2
ISOLATION BARRIER
RELAY1
RELAY4
